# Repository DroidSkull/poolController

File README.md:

# Placa controladora com 8 saidas digitais - Attiny85

### Placa eletronica com 8 saidas digitais, controladas pelo microcontrolador ATtiny85
### As saidas digitais pode ser por relés (até 12V para bobina) ou transistores (para 
### o caso de cargas pequenas).
### Acomunicação pode ser feita utilizando radio frêquencia com um modulo pronto de 
### 433MHz ou com o modulo WiFi ESP-01.
### A alimentação da placa pode ser feita com 12V e 5V desde que o seletor de tensão 
### esteja ajustado para a tensão de entrada.

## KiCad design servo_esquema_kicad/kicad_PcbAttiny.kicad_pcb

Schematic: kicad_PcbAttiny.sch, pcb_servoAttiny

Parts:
C1: 0.1u; CP_Radial_D5.0mm_P2.50mm
C2: 10u; CP_Radial_D5.0mm_P2.50mm
D1, D2, D3, D4, D5, D6, D7, D8: 1N4007; D_DO-41_SOD81_P10.16mm_Horizontal
J1: Conn_02x02_Odd_Even
J2: RF; PinSocket_1x04_P2.54mm_Vertical
J3: ESP01; PinSocket_2x04_P2.54mm_Vertical
J4, J5, J6, J7, J8, J9, J10, J11: Conn_01x04; TerminalBlock_bornier-4_P5.08mm
K1, K2, K3, K4, K5, K6, K7, K8: SANYOU_SRD_Form_C; Relay_SPDT_SANYOU_SRD_Series_Form_C
Q1, Q2, Q3, Q4, Q5, Q6, Q7, Q8: 2N2219; TO-92
R1: 220R; R_Axial_DIN0207_L6.3mm_D2.5mm_P10.16mm_Horizontal
R2: 360R; R_Axial_DIN0207_L6.3mm_D2.5mm_P10.16mm_Horizontal
R3: 2k
R4: 1k
R5, R6, R7, R8, R9, R10, R11, R12: 1k; R_Axial_DIN0207_L6.3mm_D2.5mm_P10.16mm_Horizontal
U1: ATtiny85V-10PU; DIP-8_W7.62mm_Socket
U2: LM317; TO-220-3_Horizontal_TabDown
U3: 74HC595; DIP-16_W7.62mm_Socket

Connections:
/+3.3V: C2.1, J2.1, J3.8, R2.2, U2.2
/+5V: Q1.3, Q2.3, Q3.3, Q4.3, Q5.3, Q6.3, Q7.3, Q8.3, U3.10, U3.16
/EN: J3.4, U1.1 (~RESET~/PB5)
/K1: D2.1, K2.5, Q1.1
/K2: D4.1, K4.5, Q3.1
/K3: D6.1, K6.5, Q5.1
/K4: D8.1, K8.5, Q7.1
/K5: D1.1, K1.5, Q2.1
/K6: D3.1, K3.5, Q4.1
/K7: D5.1, K5.5, Q6.1
/K8: D7.1, K7.5, Q8.1
/Q1: Q1.2, R5.2
/Q2: Q3.2, R6.2
/Q3: Q5.2, R7.2
/Q4: Q7.2, R8.2
/Q5: Q2.2, R9.2
/Q6: Q4.2, R10.2
/Q7: Q6.2, R11.2
/Q8: Q8.2, R12.2
/RX: J2.3, J3.7, U1.2 (XTAL1/PB3)
/TX: J2.2, J3.2, U1.3 (XTAL2/PB4)
GND: D1.2, D2.2, D3.2, D4.2, D5.2, D6.2, D7.2, D8.2, J2.4, J3.1, K1.2, K2.2, K3.2, K4.2, K5.2, K6.2, K7.2, K8.2, U1.4 (GND), U3.8, U3.13
unnamed: C1.1, U2.3
unnamed: C1.2, C2.2, R1.2
unnamed: J4.1, K1.4
unnamed: J4.2, K1.3
unnamed: J4.4, K1.1
unnamed: J5.1, K2.4
unnamed: J5.2, K2.3
unnamed: J5.4, K2.1
unnamed: J6.1, K3.4
unnamed: J6.2, K3.3
unnamed: J6.4, K3.1
unnamed: J7.1, K4.4
unnamed: J7.2, K4.3
unnamed: J7.4, K4.1
unnamed: J8.1, K5.4
unnamed: J8.2, K5.3
unnamed: J8.4, K5.1
unnamed: J9.1, K6.4
unnamed: J9.2, K6.3
unnamed: J9.4, K6.1
unnamed: J10.1, K7.4
unnamed: J10.2, K7.3
unnamed: J10.4, K7.1
unnamed: J11.1, K8.4
unnamed: J11.2, K8.3
unnamed: J11.4, K8.1
unnamed: R1.1, R2.1, U2.1
unnamed: R5.1, U3.15
unnamed: R6.1, U3.1
unnamed: R7.1, U3.2
unnamed: R8.1, U3.3
unnamed: R9.1, U3.4
unnamed: R10.1, U3.5
unnamed: R11.1, U3.6
unnamed: R12.1, U3.7
unnamed: U1.5 (AREF/PB0), U3.11
unnamed: U1.6 (PB1), U3.14
unnamed: U1.7 (PB2), U3.12

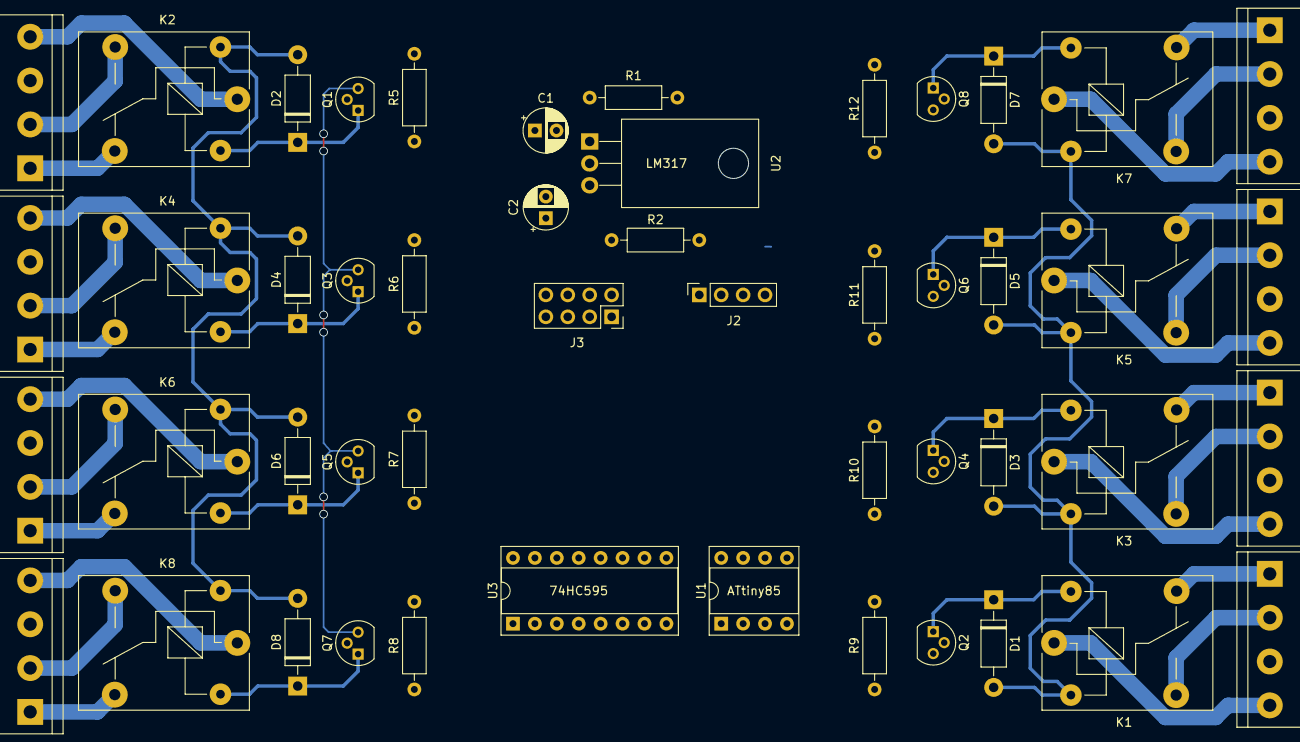
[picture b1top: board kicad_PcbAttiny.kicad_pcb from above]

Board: 2 copper layers, 49 parts (0 on the bottom side), 60 nets.

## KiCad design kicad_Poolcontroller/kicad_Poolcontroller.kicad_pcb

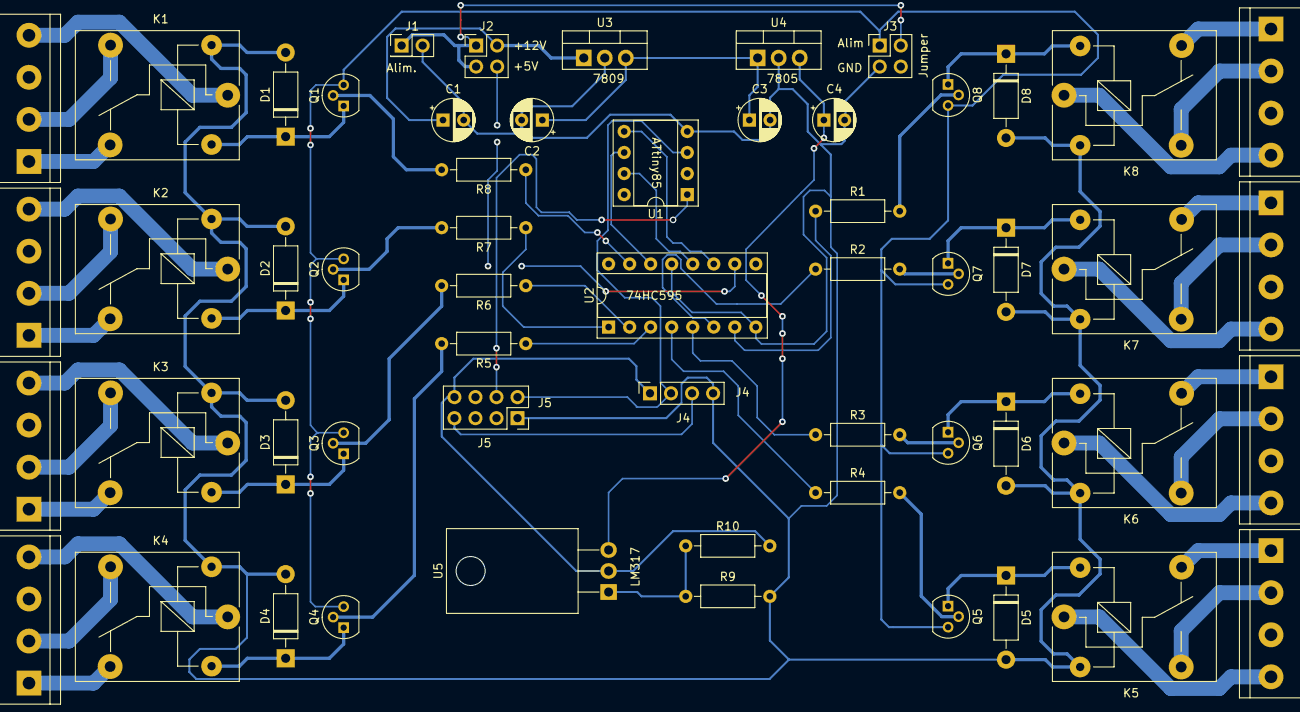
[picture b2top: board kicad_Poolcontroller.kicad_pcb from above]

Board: 2 copper layers, 56 parts (0 on the bottom side), 63 nets.

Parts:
C1, C3: 220u; CP_Radial_D5.0mm_P2.50mm
C2, C4: 47u; CP_Radial_D5.0mm_P2.50mm
D1, D2, D3, D4, D5, D6, D7, D8: 1N4007; D_DO-41_SOD81_P10.16mm_Horizontal
J1: Conn_02x01; PinHeader_2x01_P2.54mm_Vertical
J2, J3: Conn_02x02_Odd_Even; PinHeader_2x02_P2.54mm_Vertical
J4: Conn_01x04; PinSocket_1x04_P2.54mm_Vertical
J5: ESP01; PinSocket_2x04_P2.54mm_Vertical
J6, J7, J8, J9, J10, J11, J12, J13: Conn_01x04; TerminalBlock_bornier-4_P5.08mm
K1, K2, K3, K4, K5, K6, K7, K8: SANYOU_SRD_Form_C; Relay_SPDT_SANYOU_SRD_Series_Form_C
Q1, Q2, Q3, Q4, Q5, Q6, Q7, Q8: 2N2219; TO-92
R1, R2, R3, R4, R5, R6, R7, R8: 1k; R_Axial_DIN0207_L6.3mm_D2.5mm_P10.16mm_Horizontal
R9: 220R; R_Axial_DIN0207_L6.3mm_D2.5mm_P10.16mm_Horizontal
R10: 360R; R_Axial_DIN0207_L6.3mm_D2.5mm_P10.16mm_Horizontal
U1: ATtiny85V-10PU; DIP-8_W7.62mm_Socket
U2: 74HC595; DIP-16_W7.62mm_Socket
U3: L7809; TO-220-3_Vertical
U4: L7805; TO-220-3_Vertical
U5: LM317; TO-220-3_Horizontal_TabDown

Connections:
+12V: J1.1, J2.1, J2.3, J3.2
/+3.3V: J4.1, J5.8, R10.2, U5.2
/+5V: J2.4, U2.10, U2.16
/EN: J5.4, U1.1
/K1: D1.1, K1.5, Q1.1
/K2: D2.1, K2.5, Q2.1
/K3: D3.1, K3.5, Q3.1
/K4: D4.1, K4.5, Q4.1
/K5: D5.1, K5.5, Q5.1
/K6: D6.1, K6.5, Q6.1
/K7: D7.1, K7.5, Q7.1
/K8: D8.1, K8.5, Q8.1
/Q1: Q1.2, R8.2
/Q2: Q2.2, R7.2
/Q3: Q3.2, R6.2
/Q4: Q4.2, R5.2
/Q5: Q5.2, R4.2
/Q6: Q6.2, R3.2
/Q7: Q7.2, R2.2
/Q8: Q8.2, R1.2
/RX: J4.3, J5.7, U1.2
/TX: J4.2, J5.2, U1.3
GND: C1.2, C2.2, C3.2, C4.2, D1.2, D2.2, D3.2, D4.2, D5.2, D6.2, D7.2, D8.2, J1.2, J3.3, J4.4, J5.1, K1.2, K2.2, K3.2, K4.2, K5.2, K6.2, K7.2, K8.2, R9.2, U1.4, U2.8, U2.13, U3.2, U4.2
unnamed: C1.1, J2.2, U3.1
unnamed: C2.1, C3.1, U3.3, U4.1
unnamed: C4.1, U4.3, U5.3
unnamed: J3.1, Q1.3, Q2.3, Q3.3, Q4.3, Q5.3, Q6.3, Q7.3, Q8.3
unnamed: J6.1, K4.4
unnamed: J6.2, K4.3
unnamed: J6.4, K4.1
unnamed: J7.1, K3.4
unnamed: J7.2, K3.3
unnamed: J7.4, K3.1
unnamed: J8.1, K2.4
unnamed: J8.2, K2.3
unnamed: J8.4, K2.1
unnamed: J9.1, K1.4
unnamed: J9.2, K1.3
unnamed: J9.4, K1.1
unnamed: J10.1, K5.4
unnamed: J10.2, K5.3
unnamed: J10.4, K5.1
unnamed: J11.1, K6.4
unnamed: J11.2, K6.3
unnamed: J11.4, K6.1
unnamed: J12.1, K7.4
unnamed: J12.2, K7.3
unnamed: J12.4, K7.1
unnamed: J13.1, K8.4
unnamed: J13.2, K8.3
unnamed: J13.4, K8.1
unnamed: R1.1, U2.7
unnamed: R2.1, U2.6
unnamed: R3.1, U2.5
unnamed: R4.1, U2.4
unnamed: R5.1, U2.3
unnamed: R6.1, U2.2
unnamed: R7.1, U2.1
unnamed: R8.1, U2.15
unnamed: R9.1, R10.1, U5.1
unnamed: U1.5, U2.11
unnamed: U1.6, U2.14
unnamed: U1.7, U2.12

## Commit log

2021-03-24 Create kicad_Poolcontroller
2021-05-17 1.01
    retirada da possibilidade de alimentar a placa inteira com 12V
2021-05-17 1.0.2
    adicionado o divisor de tensão para o TX dos módulos de comunicação
2021-08-02 retirada de componentes desnecessarios
    após analise vi q vários componentes n tinham razão pra existir então foram retirado
2021-08-02 atualizações do esquematico e design PCB
    Atualizada o esquemático com as novas conexões p/ os transistores
    Atualizado o designe PCB com os novos footprints
2021-08-02 init design PCB
2021-08-02 trilhas terminadas
    Falta as vias para as saídas dos transistores.
2021-09-10 Atualização do circuito
2021-11-29 updata poolcontroller
